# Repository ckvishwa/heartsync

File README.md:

# heartsync

Two matching, cloud-synced pixel-art devices for a couple. A heart sent from one
lights up the other. Working name; rename freely.

**Status:** Phases 1 (Display) and 2 (Cloud sync) of 11. See [docs/phases.md](docs/phases.md).

## Layout

| Folder      | What                                                        |
|-------------|-------------------------------------------------------------|
| `firmware/` | ESP32 firmware (PlatformIO, Arduino, C++17)                 |
| `cloud/`    | Firebase: rules, Cloud Functions (TypeScript), emulator     |
| `app/`      | Flutter app (iOS and Android)                               |
| `web/`      | Next.js dashboard: devices, pixel editor, OTA releases      |
| `cad/`      | Enclosure parameters, Fusion 360 scripts, print profiles    |
| `tools/`    | Repo-wide scripts (PNG to bitmap, couple seeding)           |
| `docs/`     | PRD, architecture, phases, protocol, ADRs, hardware notes   |

## Quick start

```sh
# Firmware (PlatformIO lives in the repo-local .venv)
python -m venv .venv && .venv/Scripts/pip install platformio cryptography pillow
cp firmware/include/secrets.example.h firmware/include/secrets.h   # then edit Wi-Fi
cd firmware && pio run && pio test -e native

# Cloud (emulators, offline, project id demo-heartsync)
cd cloud && npm install && npm --prefix functions install
npm run emulators          # terminal 1
npm run seed               # terminal 2: demo users, couple, devices
npm test                   # rules + sendHeart tests

# App (with the emulators running)
cd app && flutter run

# Web (with the emulators running)
cd web && npm install && npm run dev
```

Demo logins after seeding: `alice@example.com` and `bob@example.com`, password `heartsync`.

Start with [docs/prd.md](docs/prd.md), then [docs/architecture.md](docs/architecture.md).

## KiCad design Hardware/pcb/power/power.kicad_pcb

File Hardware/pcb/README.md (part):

# Ansonia rev A custom boards (rev G shell, 190 x 76 x 35.5)

Status (2026-11-23, after review 3): **schematics done (ERC 0 errors / 0 warnings on all four), placement done, routing INCOMPLETE:**
only the touch strip is routed; the carrier has its RF lines only; the power board and most of the carrier are not routed. See "Routing status".
DRC/ERC reports are in each board folder (`<board>_DRC.rpt`, `<board>_ERC.rpt`).

## Routing status (honest summary)

| Board | State |
|---|---|
| front_touch | **routed**, GND stitched; DRC: only `copper_sliver` from the hatched pour. Gerbers/BOM/CPL in `fab/` (still unverified by a fab DFM check). |
| front_sensor | routed with GND in the autorouter; **6 connections still open** (GND pads/zone islands, `front_sensor_DRC.rpt`). Gerbers withheld. |
| carrier | **only the three RF lines are routed** (hand-routed, DRC clean: no shorts/clearance; `tools/handroute.py`). The other 262 connections are **unrouted**. Freerouting 2.1.0 stalls at 110 unrouted (168 with the 0.5 mm power widths) and never ends, so no result could be imported. Gerbers withheld. |
| power | placement + In2 BAT_SW plane only: **unrouted** (210 connections). Freerouting not run on it (same stall expected). Gerbers withheld. |

What I would do next (not done): fan out the fine-pitch parts by hand (ESP32, SIM7080G, TCA9554s, TPS61088, IP5356M), pour +3V3/VSYS on In2 on the carrier,
hand-route PVDD / QB / IP_LX / BAT_* on the power board, then autoroute the remainder with a hard pass limit (the jar ignores `-mp`).
Tools: `tools/handroute.py`, `tools/route.py` (Freerouting 2.1.0 jar via DSN/SES, GND poured not routed, width cap per board), `tools/stitch.py`
(GND / pad stitching vias, pruned by DRC), `tools/export.py` (schematic PDF, Gerber+drill zip, JLCPCB BOM/CPL, renders).
Freerouting v2.5.0's CLI crashes (native-image serialization error) and v2.3+ needs Java 25, so the v2.1.0 jar from the project's GitHub release
(66,978,394 bytes, git-ignored `_vendor/freerouting/`) is used. RF width 0.2 mm is an estimate: recompute with the JLCPCB impedance calculator
for the real 1.0 mm 4-layer stack-up. Pi-match shunt pads (DNP) are connected by the autorouter later, not yet.

## DRC / ERC summary (reports in each board folder)

| Board | ERC err / warn | DRC items (refilled zones, schematic parity on) |
|---|---|---|
| carrier | 0 / 0 | silk_edge_clearance 6, silk_over_copper 151, silk_overlap 98, starved_thermal 3, unconnected_items 262 |
| power | 0 / 0 | isolated_copper 15, silk_edge_clearance 1, silk_over_copper 163, silk_overlap 103, starved_thermal 12, unconnected_items 220 |
| front_sensor | 0 / 0 | silk_over_copper 8, silk_overlap 6, starved_thermal 2, unconnected_items 6 |
| front_touch | 0 / 0 | copper_sliver 4 |

No courtyard, edge, drill, short or hole errors remain on any board; `unconnected_items` is the unrouted work above, the rest is silkscreen and starved thermals (cosmetic / to review).

## Layout of this folder

| Path | What |
|---|---|
| `carrier/`, `power/`, `front_sensor/`, `front_touch/` | One KiCad 10 project each (`.kicad_pro/.kicad_sch/.kicad_pcb`), ERC/DRC reports, `fab/` snapshots |
| `lib/ansonia.kicad_sym`, `lib/ansonia.pretty` | Project symbols and footprints (sources below) |
| `tools/` | Generators: the Python files ARE the source of the schematics and placement |
| `_vendor/` | Downloaded datasheets / vendor footprints (git-ignored, re-download from the links below) |

Regenerate (KiCad closed):

```
cd Hardware/pcb/tools
python build_sch.py                       # schematics + ERC + netlist cross-check (all boards)
"C:\Program Files\KiCad\10.0\bin\python.exe" lib_build_fp.py      # footprints (only if lib changed)
"C:\Program Files\KiCad\10.0\bin\python.exe" pcb_build.py carrier # board: outline, holes, placement
python snap.py carrier                    # placement PNGs + DRC (refills zones, schematic parity)
```

`designs.py` = circuits (values and their datasheet sources are in the sheet notes), `boards.py` =
outlines, holes, keep-outs, placement in **device mm** (origin = device centre, +X right end, +Y top
edge, seen from the front; KiCad origin (100, 100), Y flipped). Every board has F.Cu facing the front wall.
After routing starts, rebuild with `--keep-placement` (or stop regenerating the PCB and edit in KiCad).

## Boards

| Board | Outline (device mm) | Size | Stack | Notes |
|---|---|---|---|---|
| Carrier | X -62..+28, Y -17.5..+30 | 90 x 47.5 | 4L 1.0 mm (F sig / In1 GND / In2 PWR / B sig+GND) | grew left over the old SIM-board spot; all parts on the front side |
| Power | X 30..73 (Y > -1), X 30..66.5 (Y < -1), Y -16..+33 | 43 x 49 | 4L 1.6 mm, 2 oz outer | plain outline (lid notch removed: the lid is clipped, no screws); USB-C cut-outs in the top edge |
| Front sensor | X -72.0..-60.4, Y 24.0..34.3 | 11.6 x 10.3 | 2L 0.8 mm | 8 solder pads (1.2 mm pitch, back side) replace the JST: smaller than before (13.3 x 11.8) |
| Touch strip | X -56..-16, Y 27.25..32.25 | 40 x 5 | 2L 0.8 mm | no tab: 2 solder pads on the back at the right end |

### What moved vs the fit map / brief

- **Carrier mounting holes:** H1 (-41, 21) -> (-41, 20.5); H2 (-41, 4) unchanged; **H3 (1.5, 16) -> (-9, 16)**
  (the SIM7080G sits there now); **H4 (4.5, -12) -> (9, -12.5)** (clears the e-paper FPC). The bracket frame must follow.
- **Carrier connectors:** J1 right edge (24.6, 12.5) 20-pin; J4 spk L left edge (-58.7, -7); J6 haptic bottom
  (-50, -14.2); J7 touch (-46.5, 26.6); J8 front sensor (-56, 26.6); J9 mute LED (-58.7, -13.5); J11 panel FPC
  (-25.5, -13.4); J12 buttons (-38.35, 26.6); J13 e-paper FPC (-4, -13.4, DNP); J14 nano-SIM (20.5, -9.5).
  **Dropped:** J2 (cell sense: the PD IC gauges the cell over I2C), J3 (SIM board is now on the carrier),
  J5 (speaker R plugs into the power board, J7 there, next to the amp), J10 (gesture shares J8 with the mic:
  one front board, one cable).
- **Lid (review 1):** no screws any more (gasket + 8 snap clips at Z 0..4 + a hook into each speaker box). The boss
  notch and keep-outs are deleted; the power board is a full rectangle again.
- **Review-1 changes:** J1 is now 22-pin (adds QI_EN, PWR_KEY; footprint `ansonia:JST_SH_SM22B...` made from KiCad's
  SM20B, **verify against the JST drawing**); J5 dropped (NTC on J4); IMU U12 added; J13 e-paper fitted with booster.
- **USB-C ports:** centres X +52.75 / +66.05 as briefed, but the footprint puts the board edge 0.25 mm further
  out than Amphenol's drawing so the rear shell legs keep 0.3 mm copper-to-edge (Amphenol's layout has 0.05 mm).
  The port mating face therefore sits 0.25 mm further inside: check against the wall opening.

### Connector rule (review 2)

Wires are soldered straight to the small remote boards/parts (front sensor, touch strip, buttons, haptic LRA, mute LED): no connector on
that end. The carrier keeps one JST SH per remote (J8 front sensor 8-pin, J7 touch 2-pin, J12 buttons 6-pin, J6 haptic 2-pin, J9 mute LED
2-pin) so it can come out. Kept as connectors: U.FL x 4 antennas, FPC for the OLED (J11) and e-paper (J13), carrier-to-power J1, speakers
(carrier J4, power J7). Wire pads: `ansonia:WirePads_1x08_P1.20mm` (1.0 x 2.0 mm) and `_1x02_P1.60mm`.
Battery: **Amass MR30PW-M** on the power board J4 (left edge, mating face flush with X 30) plus a 2-pin SH (J5) for the NTC. The MR30 is a
3-pole part (the spec sheet I found: 15 A, 3.5 mm pitch, 3 x d1.9 holes + 2 x d1.0 locating holes); BAT+ on pin 1, BAT- on pin 3, pin 2
open. The 2-pin Amass part is the XT30: say if you meant that. Footprint holes are from the Amass drawing, body outline and the
locating-hole row position (10 mm from the pins) are my reading of it: **verify before fab**. The BAT solder pads were removed.

## Key circuit decisions (detail in the schematic sheet notes)

- **3 x TCA9554** (0x20 outputs, 0x21 buttons/status inputs, 0x22 Bluetooth control). The brief's expander list
  needs 20 I/O (6 outputs + 6 inputs + 4 BT PIOs + BT reset, SIM DTR, OLED VCC enable, mute LED); one TCA9554 has 8.
  Outputs that must be off at power-up have 10k pull-downs (TCA9554 inputs float high on 100k).
- **SIM7080G UART is 1.8 V** (VDD_EXT): TXB0104 between it and the ESP32 (TX, RX, STATUS, DTR). PWRKEY via MMBT3904.
- **Bluetooth antenna:** EWM104 pin 46 is a 50 ohm stamp hole and the module has **no antenna** (Ebyte manual 2.1).
  U.FL J17 + pi pads for a 2.4 GHz FPC antenna. Where that antenna goes is open.
- **ESP32 pin map:** checked against the WROOM-1U datasheet, no clash (IO35-37 unused, straps unused, IO19/20 USB).
  Spare: IO1, IO2 (test pads). USB D+/D- reach the ESP32 through J1 from USB-C port 1 for flashing.
- **12 V panel supply:** TPS61040 behind a P-FET switch so VCC floats when off (SSD1322 sec. 8.9).
- **Amp boost:** TPS61088 at **9.0 V** (499k / 76.8k), PWM mode, 600 kHz, values from the datasheet equations (sheet note). Amp limit 4 W/ch (see power budget).
- **Battery path:** MR30 J4 (BAT+ pin 1, BAT- pin 3; DNP 4x4 pads TP1/TP2 as an 18 AWG alternative) -> 8 A fuse -> reverse-battery P-FET
  (DMP3013SFV) -> BAT_SW (5 V TVS). Pack NTC on JST SH J5. **The IP5356M's VSYS pins are its internal 5-12 V DC-DC bus, not a system rail**:
  the system rail VSYS is the battery (BAT_SW) through a fitted 0R. Consequence: the system loads bypass the IC, so its fuel gauge does
  not see them and charge termination sees battery current net of the load. J1 now says VSYS = 3.0-4.2 V.
- **IMU (U12 LSM6DSOX, LGA-14):** I2C 0x6A (SA0 = GND, CS = VDDIO), INT1 -> ESP32 IO3 (RTC GPIO3, 100k pull-down so it is low at boot;
  IO3 is the JTAG-source strap, left at its default), INT2 -> TCA9554 0x21 P7. Placed at (-10, 8) mid-board, far from the speaker magnets.
  I2C map, no clash: 0x20/21/22 TCA9554, 0x2C TAS5805M, 0x39 APDS-9960, 0x5A DRV2605L, 0x6A LSM6DSOX; the power IC's address is TBD.
  Aux pins, from ST DS12814 rev 3 table 2 (p. 9), Mode 1 (aux SPI not used): pin 2 SDx and pin 3 SCx "Connect to VDDIO or GND" -> GND;
  pin 10 OCS_Aux "Leave unconnected" -> no connect; pin 11 SDO_Aux "Connect to VDD_IO or leave unconnected" -> VDDIO. (The pins have
  internal pull-ups, register bit "disable pull-up on OCS_Aux and SDO_Aux".) Symbol: modified KiCad LSM6DSL, identical LGA-14 pinout.
- **Qi TX:** separate 24 x 32 mm module on J6 (4-pin SH: 2 x QI_VIN 9 V, 2 x GND) with its **own TPS61088 boost (U7) and an LC filter**,
  see "Qi supply decision". Enable = QI_EN (expander 0x22 P6 over J1), which is U7's EN pin with a 10k pull-down.
- **E-paper (J13 fitted):** Waveshare 3.97inch e-Paper (G), 800 x 480, SSD2677, 24-pin 0.5 mm FPC. **Verified** against Waveshare's
  *3.97inch e-Paper (G) User Manual v1.0* (pin table sec. 5: identical to your list, pin 5 = VSH2) and the *3.97inch e-Paper HAT+ (G)* driver-board
  schematic (R1 2.2R, R2 1M, Q1 AO3400, L1 10uH, D1-D3 MBR0530, C1 4.7uF/25V on pin 5 VSH2, C2 1uF/50V on VDDIO+VCI, C4 1uF on VDD,
  C6-C9 4.7uF on VSH1/VGH/VSL/VGL, C10 1uF on VCOM, C3/C5 4.7uF). The two-colour panel has the same circuit. Pins 1/4/6/7 are NC, each its own
  net; pin 8 BS1 = GND (4-wire SPI). Differences to know: **BUSY is active low** (low = busy), **operating temperature 0..40 C**.
  FPC route (plan, not checked against the cell position in the fit map): the 24-pin tail leaves the panel's bottom edge, runs along the
  rear wall under the carrier's bottom edge (the carrier ends at Y -17.5, J13 enters from -Y) and folds once into J13; the cell and
  power board are on the +X side, so the tail should not cross the cell. Measure the tail length and fold radius on the real panel.
- **Bluetooth antenna:** 2.4 GHz FPC antenna on the inside of the BOTTOM wall, X +38..+64, Z 15..28 (above the pogo pads and the magnets
  at X +32/+70), far from the Wi-Fi PIFA (X -52..-12) and the LTE flex (top wall). J17 stays at the module (X -50): the U.FL
  cable is ~110 mm (about 1 dB at 2.4 GHz for 1.13 mm coax, estimate). It is near the Qi ferrite: test RSSI on the bench.
- **Front sensor acoustics:** the ICS-43434 library footprint already carries the 0.5 mm sound-port NPTH; it lands on (-69.5, 31.25),
  the front-wall hole. A ring-gasket outline (OD 3.6, ID 1.6) is drawn on F.Fab around it: foam/silicone ring between the PCB and the wall,
  airtight. APDS-9960 package centre at (-64, 31.25); its optical-window offset inside the package is not checked.

## IP5356M charger (review 3, item 1) - datasheet V1.00 read (IP5356M-datasheet-en-V1.00.pdf)

- **Cell count / power:** 1 cell (4.2/4.3/4.35/4.4 V), charge up to 18 W / 5 A at the battery, boost 5 V 3.1 A, 9 V 2.22 A, 12 V 1.67 A (p. 1).
- **Ports:** 2 USB-A, USB-B in, Micro/lightning in, **1 Type-C in/out** (PD2.0/3.0, PPS) and "1 USB C input/output port + 1 USB C output port
  (customize)" (p. 1). The datasheet's customised-model table (p. 10: LBZ, DBZ, DBZ_4V35, LCL, DCL1W, DCL1W_4V35) has **no dual-Type-C model
  and no part number for it**: ask Injoinic (service@injoinic.com) for the exact orderable name.
- **I2C:** only the `_L` (LED) models: **IP5356M_LBZ** (orderable at LCSC as **IP5356M_LBZ_CB, C46550232**) and IP5356M_LCL (with lightning).
  Pins: LED2 (pin 1) = SDA, LED1 (pin 40) = SCL, LED3 (pin 2) = INT; fig. 20 on p. 30: 3.3k from each of SDA/SCL to the IC's VCC and 510k from
  INT to ground; the IC enters I2C mode by itself from that wiring; INT is Hi-Z in standby and high when working. **The I2C slave address
  and the register map are NOT in this datasheet** (separate Injoinic document): not found. This design uses exactly fig. 20 and removes
  the carrier's 10k PWR_INT pull-up (it would hide the standby state).
- **NTC:** pin 22 sources 20 uA / 80 uA through the 10k NTC, 100 nF at the pin; if the NTC is absent a 10k to ground is required (p. 29-30, fig. 18).
  The pack's 10k NTC goes to J5. An unplugged J5 reads as "cold" and stops charging (safe).
- **Second Type-C (what I built):** port 2 = VOUT2 (pins 34/35, DPA2/DMA2 pins 32/33) to the J3 Type-C, 2.2 uF + 0.1 uF, Rp 22k from VBUS2 to
  CC1 and CC2 (1.5 A). Only 5 V when more than one port is on. **Open risk:** a real Type-C sink waits for VBUS before drawing current, but VOUT2
  turns on only when the IC detects a load: whether a plain Rd sink wakes it is not in the datasheet. The customised part may solve it: ask Injoinic.
- **Wiring used (datasheet fig. 25):** L1 2.2 uH LX to BAT, BST 0.1 uF to LX, VCC 2.2 uF, VSYS 6 x 22 uF (+0.1 uF), BAT 22 uF + 0.1 uF, VBUS 2 x 2.2 uF + 0.1 uF,
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
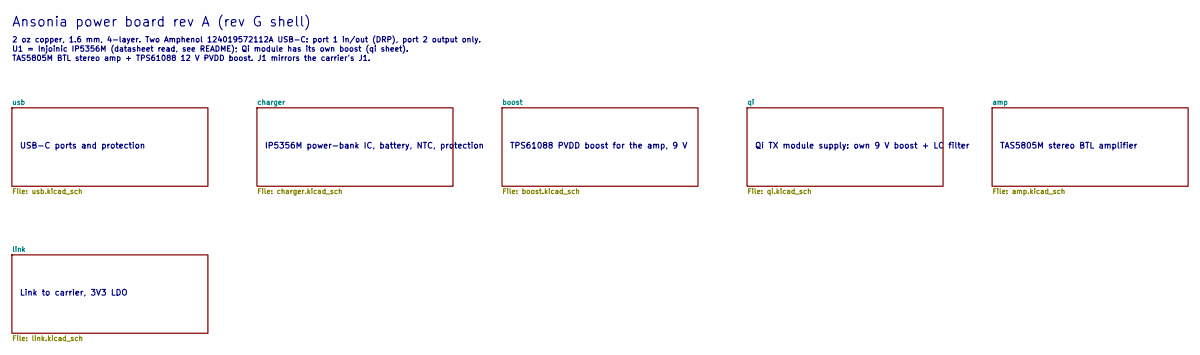
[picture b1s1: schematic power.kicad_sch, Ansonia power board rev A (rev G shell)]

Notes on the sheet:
USB-C ports and protection
IP5356M power-bank IC, battery, NTC, protection
TPS61088 PVDD boost for the amp, 9 V
Qi TX module supply: own 9 V boost + LC filter
TAS5805M stereo BTL amplifier
Link to carrier, 3V3 LDO
Ansonia power board rev A (rev G shell)
2 oz copper, 1.6 mm, 4-layer. Two Amphenol 124019572112A USB-C: port 1 in/out (DRP), port 2 output only.
U1 = Injoinic IP5356M (datasheet read, see README); Qi module has its own boost (qi sheet).
TAS5805M BTL stereo amp + TPS61088 12 V PVDD boost. J1 mirrors the carrier's J1.

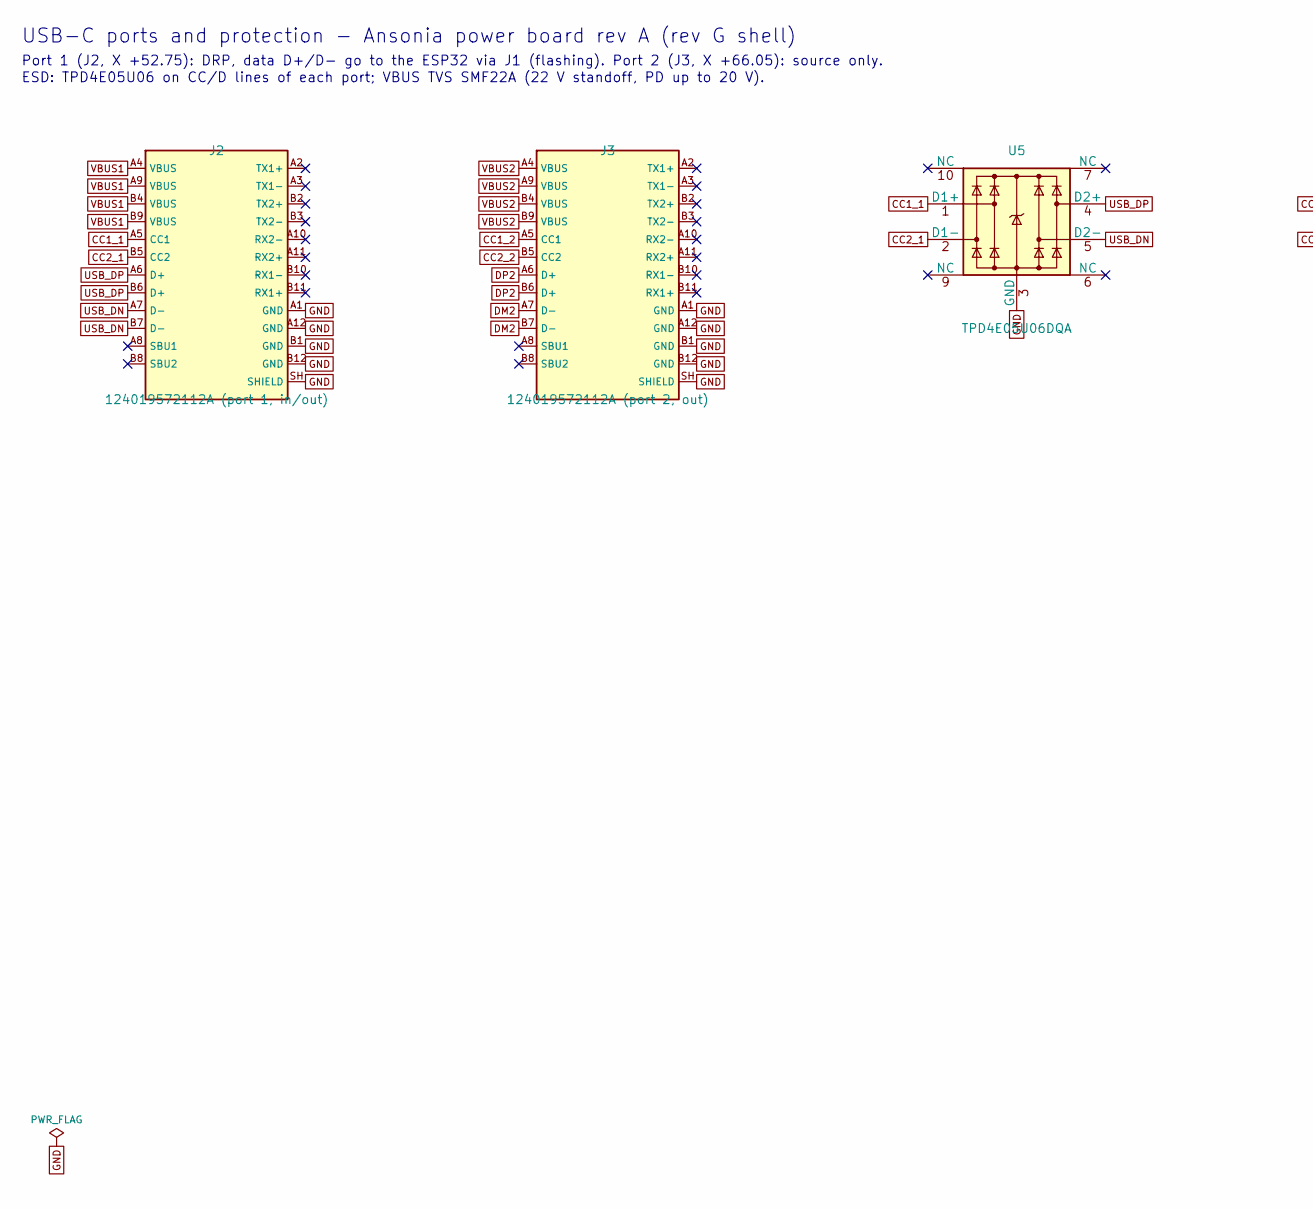
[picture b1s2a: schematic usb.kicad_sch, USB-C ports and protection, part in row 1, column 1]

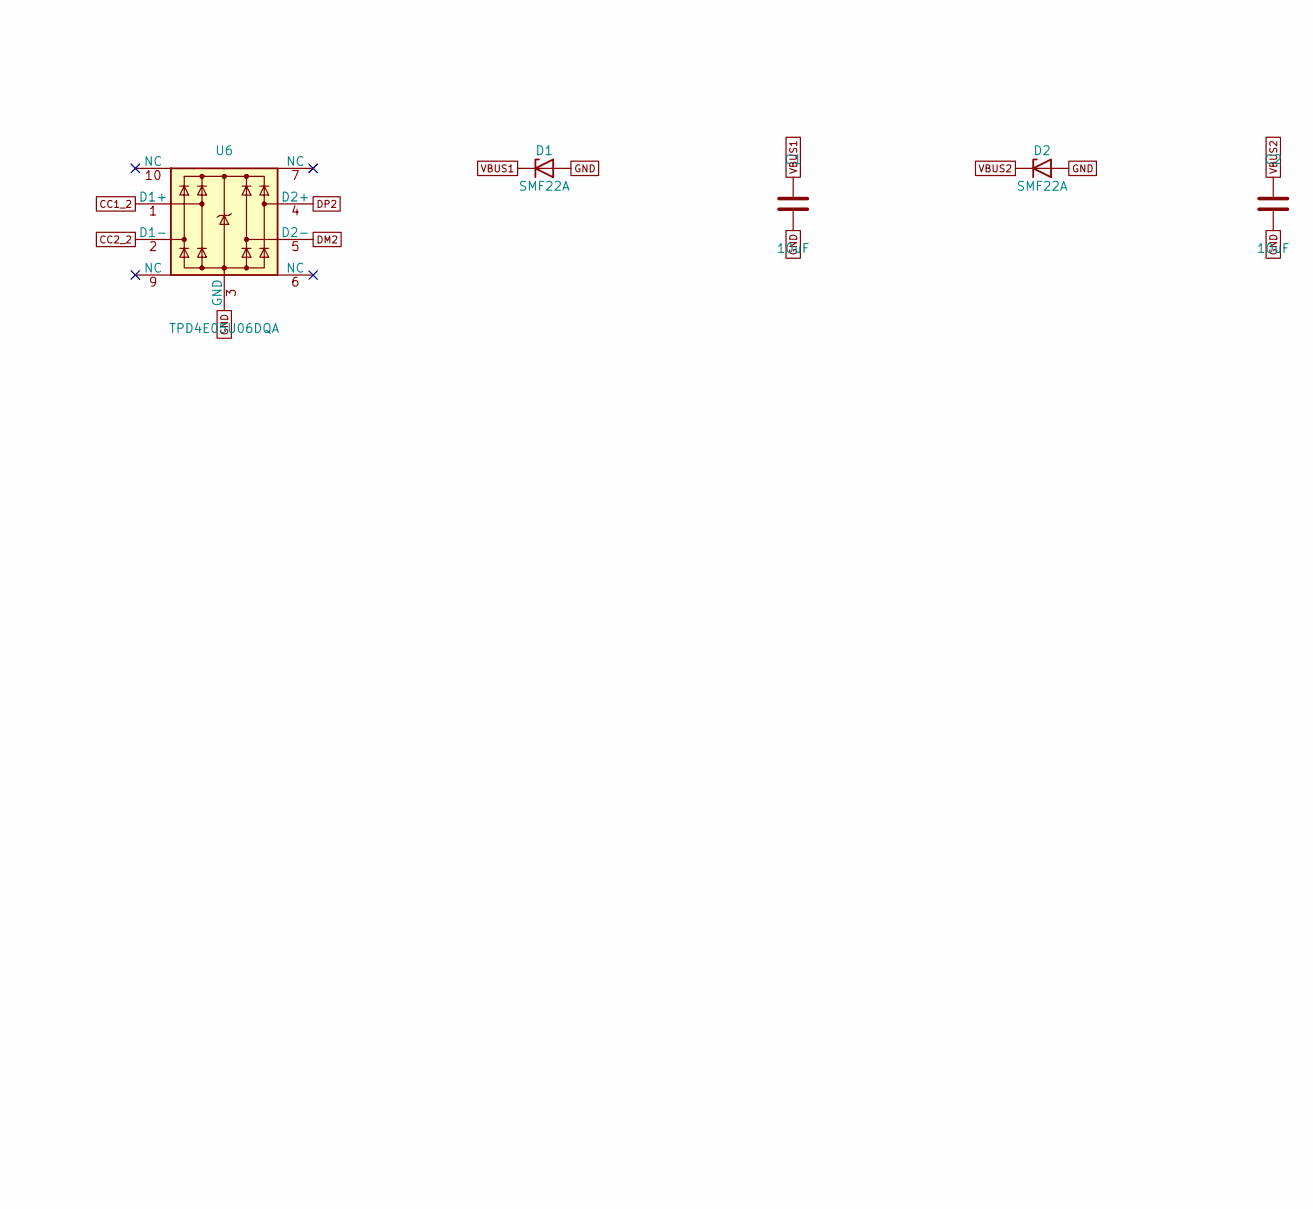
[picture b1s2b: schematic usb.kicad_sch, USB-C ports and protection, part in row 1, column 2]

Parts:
C1, C2: 10uF; C_0805_2012Metric
D1, D2: SMF22A; D_SOD-123F
J2: 124019572112A (port 1, in/out); USB_C_Amphenol_124019572112A; MPN 124019572112A
J3: 124019572112A (port 2, out); USB_C_Amphenol_124019572112A; MPN 124019572112A
U5, U6: TPD4E05U06DQA; USON-10_2.5x1.0mm_P0.5mm; MPN TPD4E05U06DQAR

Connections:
CC1_1: J2.A5 (CC1), U5.1 (D1+); also elsewhere on the board
CC1_2: J3.A5 (CC1), U6.1 (D1+); also elsewhere on the board
CC2_1: J2.B5 (CC2), U5.2 (D1-); also elsewhere on the board
CC2_2: J3.B5 (CC2), U6.2 (D1-); also elsewhere on the board
DM2: J3.A7 (D-), J3.B7 (D-), U6.5 (D2-); also elsewhere on the board
DP2: J3.A6 (D+), J3.B6 (D+), U6.4 (D2+); also elsewhere on the board
GND: C1.2, C2.2, D1.2 (A), D2.2 (A), J2.A1 (GND), J2.A12 (GND), J2.B1 (GND), J2.B12 (GND), J2.SH (SHIELD), J3.A1 (GND), J3.A12 (GND), J3.B1 (GND), J3.B12 (GND), J3.SH (SHIELD), U5.3 (GND), U5.8 (GND), U6.3 (GND), U6.8 (GND); also elsewhere on the board
USB_DN: J2.A7 (D-), J2.B7 (D-), U5.5 (D2-); also elsewhere on the board
USB_DP: J2.A6 (D+), J2.B6 (D+), U5.4 (D2+); also elsewhere on the board
VBUS1: C1.1, D1.1 (K), J2.A4 (VBUS), J2.A9 (VBUS), J2.B4 (VBUS), J2.B9 (VBUS); also elsewhere on the board
VBUS2: C2.1, D2.1 (K), J3.A4 (VBUS), J3.A9 (VBUS), J3.B4 (VBUS), J3.B9 (VBUS); also elsewhere on the board

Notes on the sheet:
USB-C ports and protection - Ansonia power board rev A (rev G shell)
Port 1 (J2, X +52.75): DRP, data D+/D- go to the ESP32 via J1 (flashing). Port 2 (J3, X +66.05): source only.
ESD: TPD4E05U06 on CC/D lines of each port; VBUS TVS SMF22A (22 V standoff, PD up to 20 V).

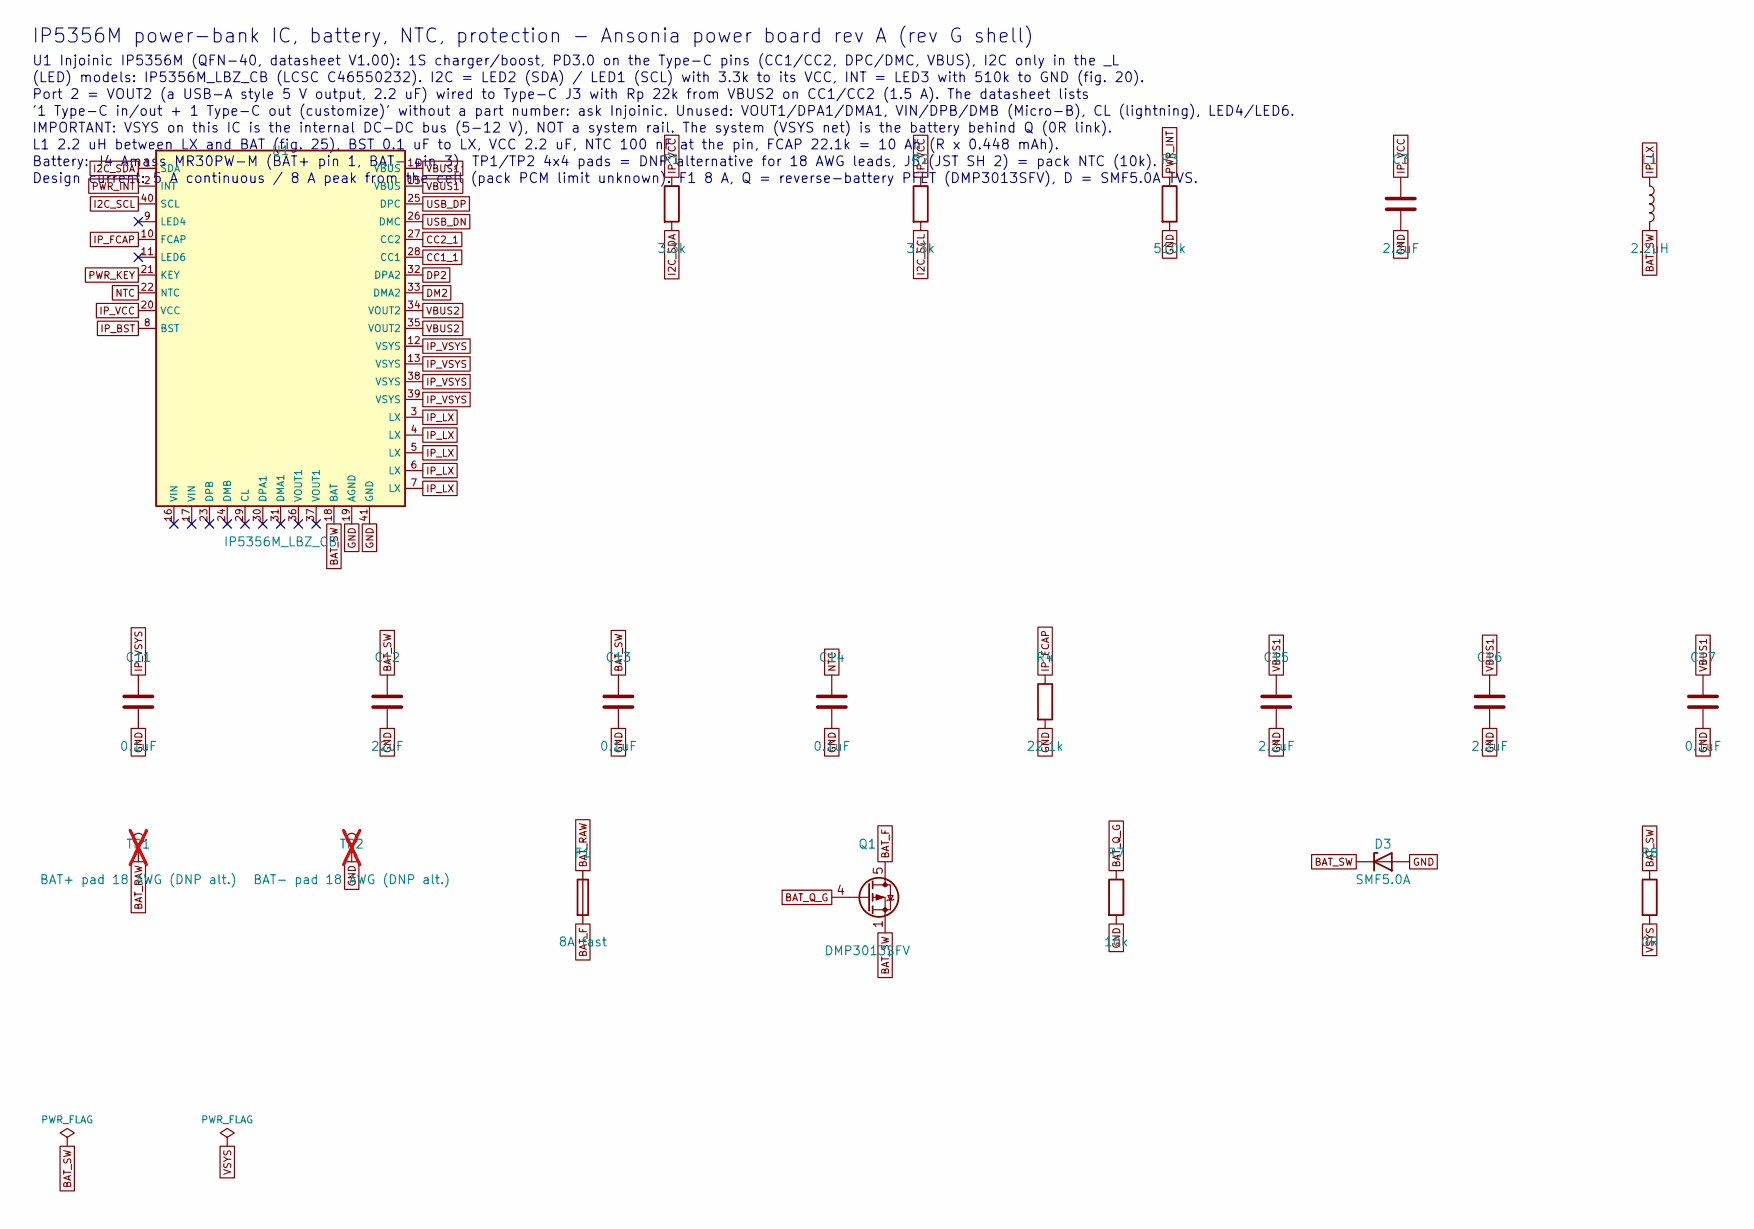
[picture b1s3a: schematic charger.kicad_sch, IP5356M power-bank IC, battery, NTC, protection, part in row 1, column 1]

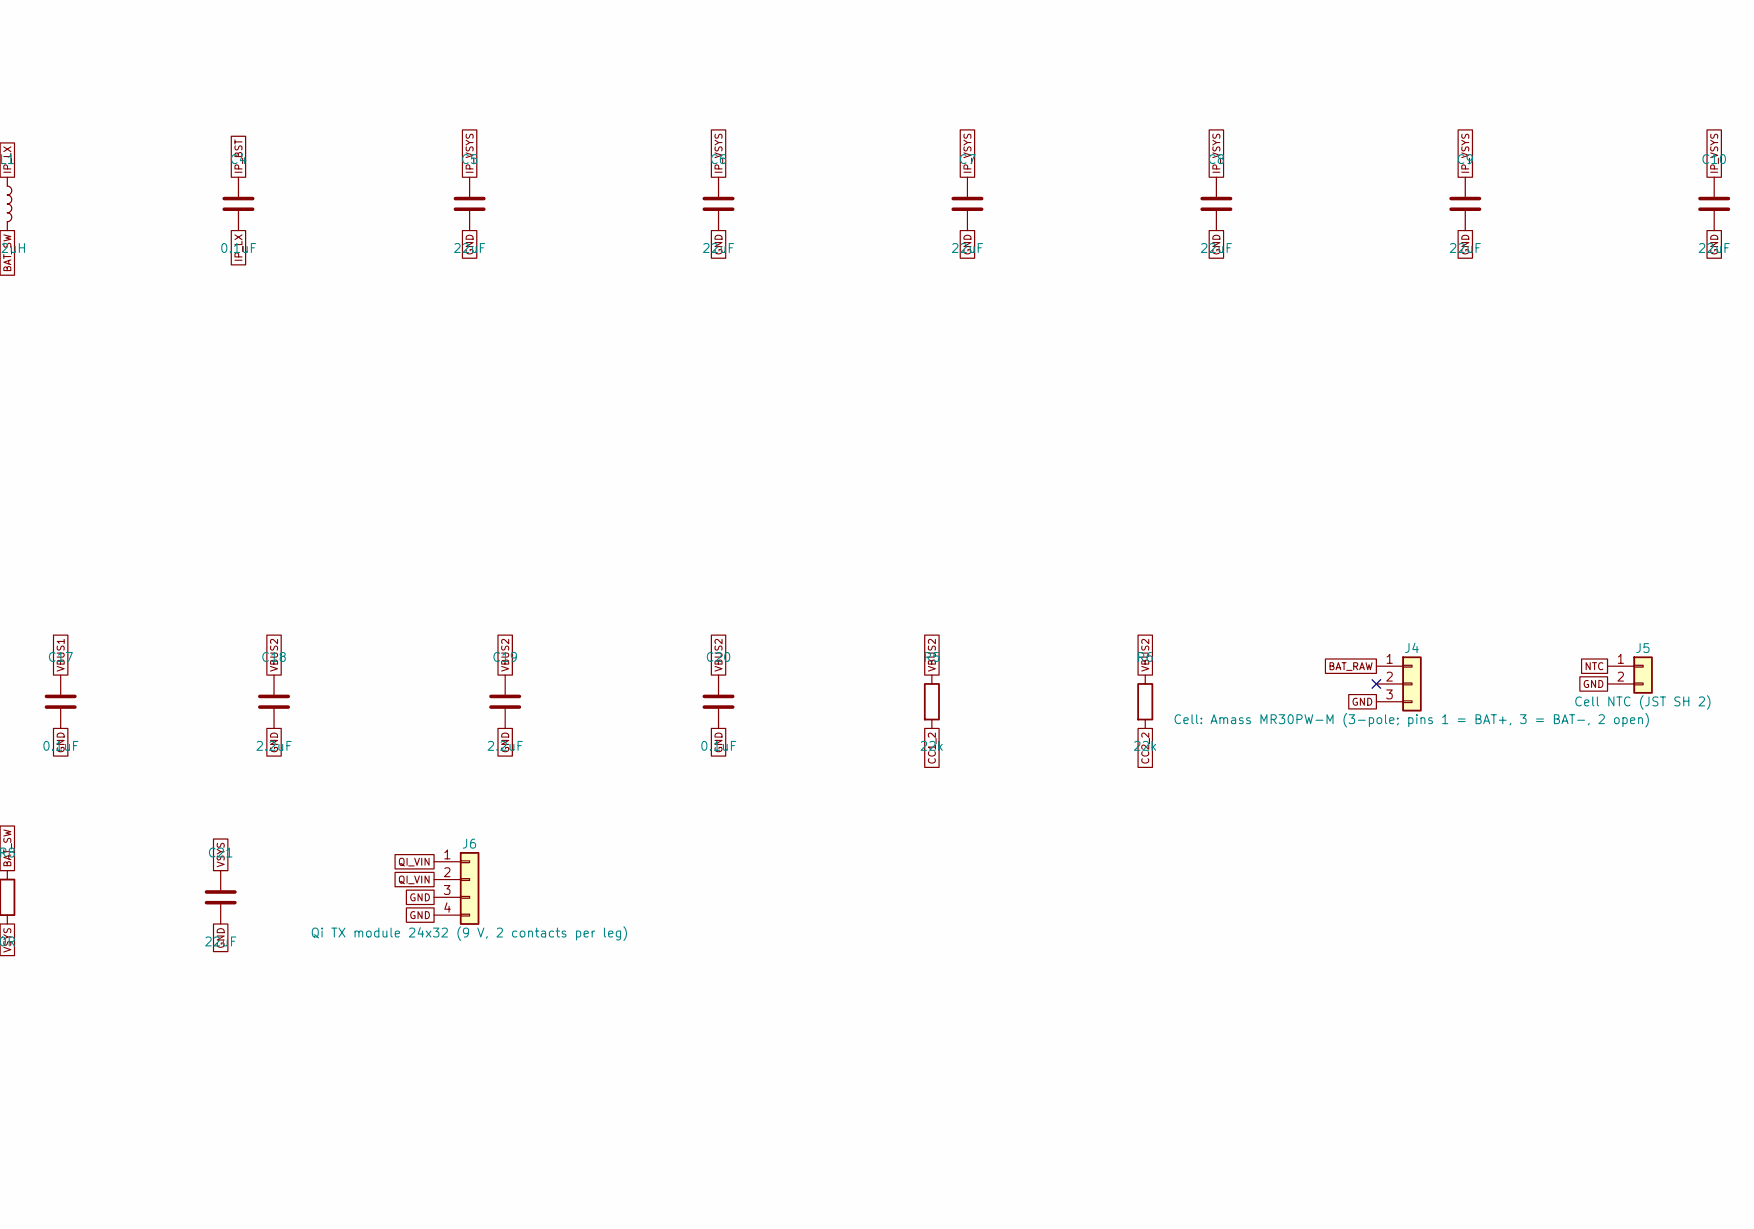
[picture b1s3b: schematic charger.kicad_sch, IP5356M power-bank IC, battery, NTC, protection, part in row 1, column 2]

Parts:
C3, C15, C16, C18, C19: 2.2uF; C_0603_1608Metric
C4, C11, C13, C14, C17, C20: 0.1uF; C_0402_1005Metric
C5, C6, C7, C8, C9, C10, C12, C21: 22uF; C_0805_2012Metric
D3: SMF5.0A; D_SOD-123F
F1: 8A fast; Fuse_1206_3216Metric; MPN 0466008.NR
J4: Cell: Amass MR30PW-M (3-pole; pins 1 = BAT+, 3 = 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; Amass_MR30PW-M_1x03_P3.50mm_Horizontal; MPN MR30PW-M
J5: Cell NTC (JST SH 2); JST_SH_SM02B-SRSS-TB_1x02-1MP_P1.00mm_Horizontal
J6: Qi TX module 24x32 (9 V, 2 contacts per leg); JST_SH_SM04B-SRSS-TB_1x04-1MP_P1.00mm_Horizontal
L1: 2.2uH; L_Bourns_SRP7028A_7.3x6.6mm; MPN SRP7028A-2R2M
Q1: DMP3013SFV; Diodes_PowerDI3333-8
R1, R2: 3.3k; R_0402_1005Metric
R3: 510k; R_0402_1005Metric
R4: 22.1k; R_0402_1005Metric
R5, R6: 22k; R_0402_1005Metric
R7: 10k; R_0402_1005Metric
R8: 0R; R_1206_3216Metric
TP1: BAT+ pad 18 AWG (DNP alt.); TestPoint_Pad_4.0x4.0mm; not fitted
TP2: BAT- pad 18 AWG (DNP alt.); TestPoint_Pad_4.0x4.0mm; not fitted
U1: IP5356M_LBZ_CB; QFN-40-1EP_6x6mm_P0.5mm_EP4.6x4.6mm; MPN IP5356M_LBZ_CB; LCSC C46550232

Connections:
BAT_F: F1.2, Q1.5 (D)
BAT_Q_G: Q1.4 (G), R7.1
BAT_RAW: F1.1, J4.1, TP1.1
BAT_SW: C12.1, C13.1, D3.1 (K), L1.2, Q1.1 (S), Q1.2 (S), Q1.3 (S), R8.1, U1.18 (BAT); also elsewhere on the board
CC1_1: U1.28 (CC1); also elsewhere on the board
CC1_2: R5.2; also elsewhere on the board
CC2_1: U1.27 (CC2); also elsewhere on the board
CC2_2: R6.2; also elsewhere on the board
DM2: U1.33 (DMA2); also elsewhere on the board
DP2: U1.32 (DPA2); also elsewhere on the board
GND: C3.2, C5.2, C6.2, C7.2, C8.2, C9.2, C10.2, C11.2, C12.2, C13.2, C14.2, C15.2, C16.2, C17.2, C18.2, C19.2, C20.2, C21.2, D3.2 (A), J4.3, J5.2, J6.3, J6.4, R3.2, R4.2, R7.2, TP2.1, U1.19 (AGND), U1.41 (GND); also elsewhere on the board
I2C_SCL: R2.2, U1.40 (SCL); also elsewhere on the board
I2C_SDA: R1.2, U1.1 (SDA); also elsewhere on the board
IP_BST: C4.1, U1.8 (BST)
IP_FCAP: R4.1, U1.10 (FCAP)
IP_LX: C4.2, L1.1, U1.3 (LX), U1.4 (LX), U1.5 (LX), U1.6 (LX), U1.7 (LX)
IP_VCC: C3.1, R1.1, R2.1, U1.20 (VCC)
IP_VSYS: C5.1, C6.1, C7.1, C8.1, C9.1, C10.1, C11.1, U1.12 (VSYS), U1.13 (VSYS), U1.38 (VSYS), U1.39 (VSYS)
NTC: C14.1, J5.1, U1.22 (NTC)
PWR_INT: R3.1, U1.2 (INT); also elsewhere on the board
PWR_KEY: U1.21 (KEY); also elsewhere on the board
QI_VIN: J6.1, J6.2; also elsewhere on the board
USB_DN: U1.26 (DMC); also elsewhere on the board
USB_DP: U1.25 (DPC); also elsewhere on the board
VBUS1: C15.1, C16.1, C17.1, U1.14 (VBUS), U1.15 (VBUS); also elsewhere on the board
VBUS2: C18.1, C19.1, C20.1, R5.1, R6.1, U1.34 (VOUT2), U1.35 (VOUT2); also elsewhere on the board
VSYS: C21.1, R8.2; also elsewhere on the board

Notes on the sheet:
IP5356M power-bank IC, battery, NTC, protection - Ansonia power board rev A (rev G shell)
U1 Injoinic IP5356M (QFN-40, datasheet V1.00): 1S charger/boost, PD3.0 on the Type-C pins (CC1/CC2, DPC/DMC, VBUS), I2C only in the _L
(LED) models: IP5356M_LBZ_CB (LCSC C46550232). I2C = LED2 (SDA) / LED1 (SCL) with 3.3k to its VCC, INT = LED3 with 510k to GND (fig. 20).
Port 2 = VOUT2 (a USB-A style 5 V output, 2.2 uF) wired to Type-C J3 with Rp 22k from VBUS2 on CC1/CC2 (1.5 A). The datasheet lists
'1 Type-C in/out + 1 Type-C out (customize)' without a part number: ask Injoinic. Unused: VOUT1/DPA1/DMA1, VIN/DPB/DMB (Micro-B), CL (lightning), LED4/LED6.
IMPORTANT: VSYS on this IC is the internal DC-DC bus (5-12 V), NOT a system rail. The system (VSYS net) is the battery behind Q (0R link).
L1 2.2 uH between LX and BAT (fig. 25), BST 0.1 uF to LX, VCC 2.2 uF, NTC 100 nF at the pin, FCAP 22.1k = 10 Ah (R x 0.448 mAh).
Battery: J4 Amass MR30PW-M (BAT+ pin 1, BAT- pin 3), TP1/TP2 4x4 pads = DNP alternative for 18 AWG leads, J5 (JST SH 2) = pack NTC (10k).
Design current: 5 A continuous / 8 A peak from the cell (pack PCM limit unknown). F1 8 A, Q = reverse-battery PFET (DMP3013SFV), D = SMF5.0A TVS.

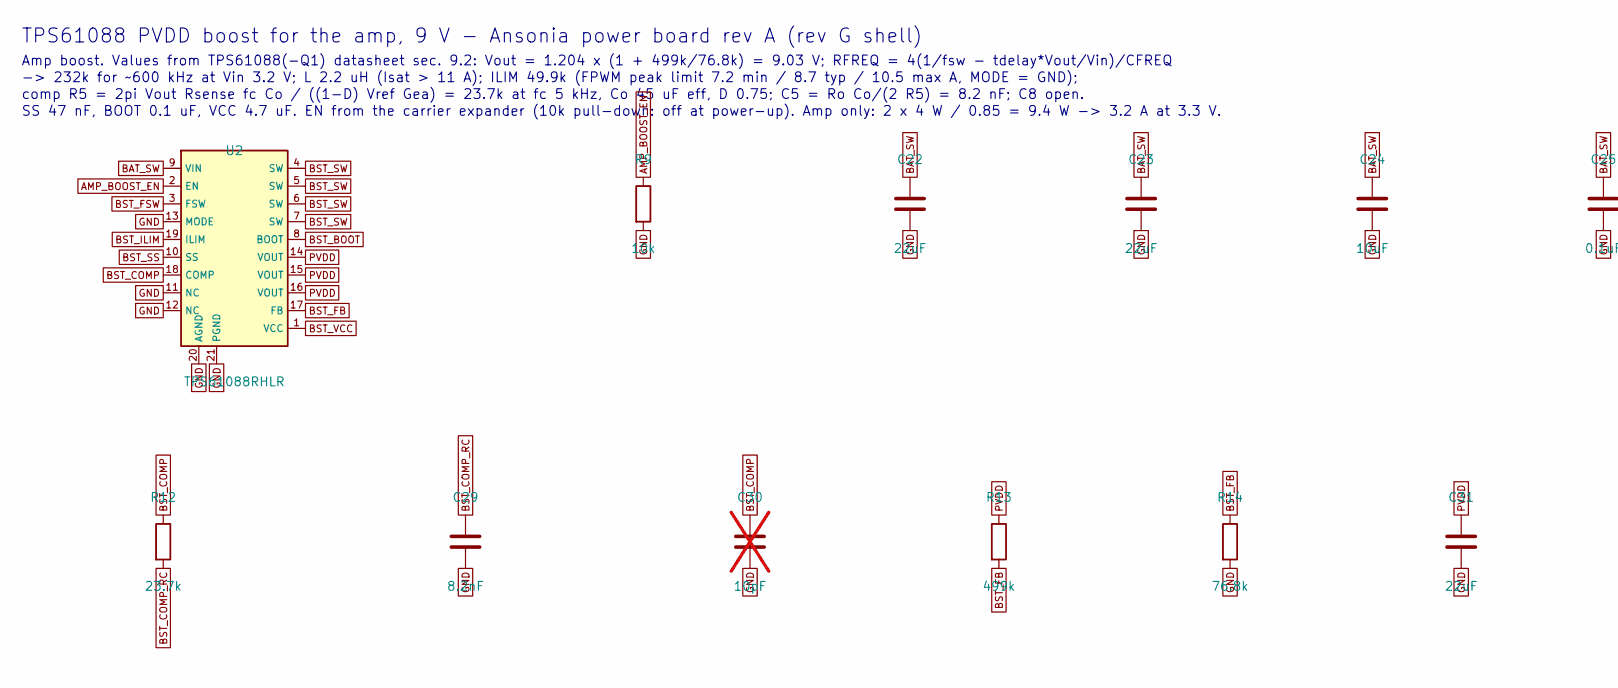
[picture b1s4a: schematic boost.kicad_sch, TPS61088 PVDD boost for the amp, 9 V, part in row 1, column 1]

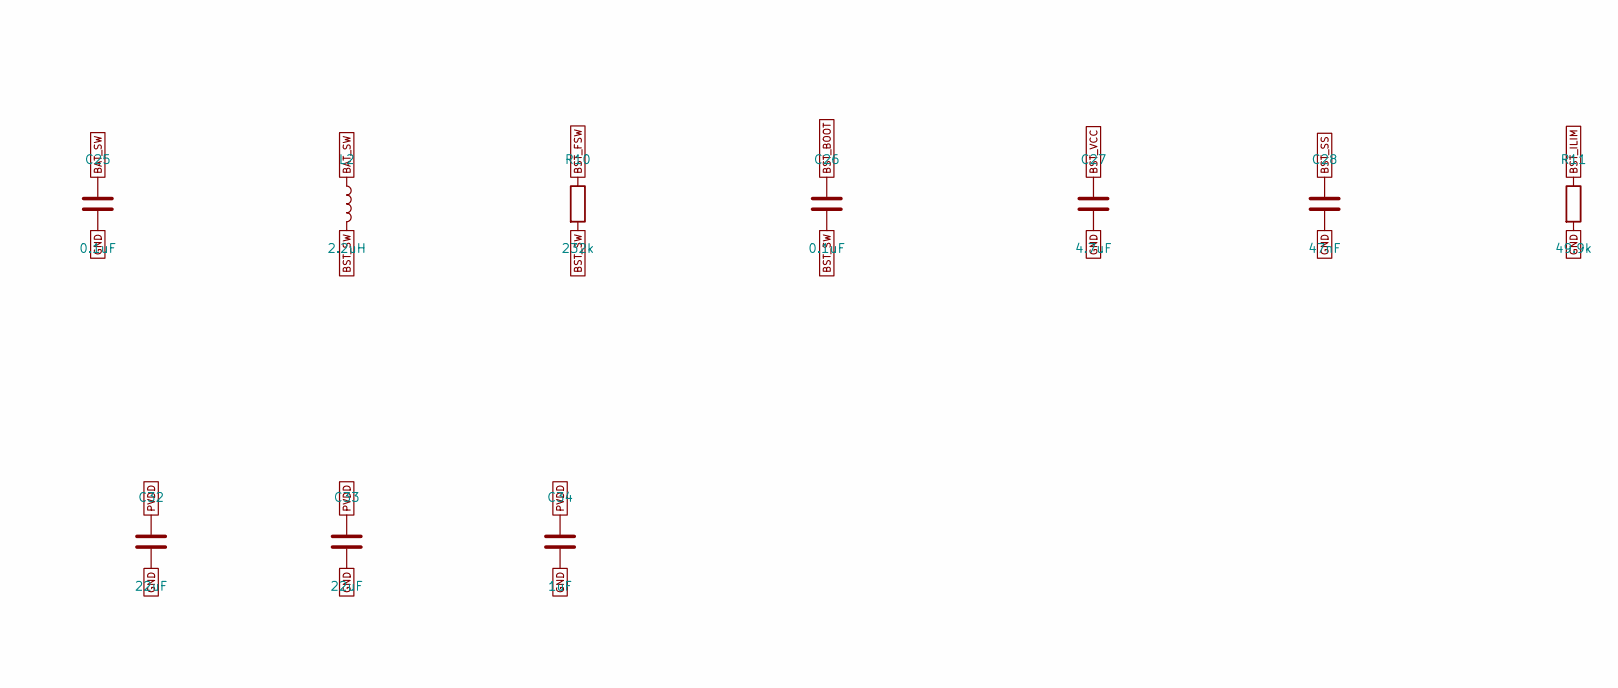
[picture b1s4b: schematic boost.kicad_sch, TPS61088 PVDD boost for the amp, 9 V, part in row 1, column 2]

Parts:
C22, C23: 22uF; C_0805_2012Metric
C24: 10uF; C_0603_1608Metric
C25, C26: 0.1uF; C_0402_1005Metric
C27: 4.7uF; C_0603_1608Metric
C28: 47nF; C_0402_1005Metric
C29: 8.2nF; C_0402_1005Metric
C30: 10pF; C_0402_1005Metric; not fitted
C31, C32, C33: 22uF; C_1206_3216Metric
C34: 1uF; C_0603_1608Metric
L2: 2.2uH; L_Bourns_SRP7028A_7.3x6.6mm; MPN SRP7028A-2R2M
R9: 10k; R_0402_1005Metric
R10: 232k; R_0402_1005Metric
R11: 49.9k; R_0402_1005Metric
R12: 23.7k; R_0402_1005Metric
R13: 499k; R_0402_1005Metric
R14: 76.8k; R_0402_1005Metric
U2: TPS61088RHLR; Texas_VQFN-RHL-20; MPN TPS61088RHLR; LCSC C88281

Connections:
AMP_BOOST_EN: R9.1, U2.2 (EN); also elsewhere on the board
BAT_SW: C22.1, C23.1, C24.1, C25.1, L2.1, U2.9 (VIN); also elsewhere on the board
BST_BOOT: C26.1, U2.8 (BOOT)
BST_COMP: C30.1, R12.1, U2.18 (COMP)
BST_COMP_RC: C29.1, R12.2
BST_FB: R13.2, R14.1, U2.17 (FB)
BST_FSW: R10.1, U2.3 (FSW)
BST_ILIM: R11.1, U2.19 (ILIM)
BST_SS: C28.1, U2.10 (SS)
BST_SW: C26.2, L2.2, R10.2, U2.4 (SW), U2.5 (SW), U2.6 (SW), U2.7 (SW)
BST_VCC: C27.1, U2.1 (VCC)
GND: C22.2, C23.2, C24.2, C25.2, C27.2, C28.2, C29.2, C30.2, C31.2, C32.2, C33.2, C34.2, R9.2, R11.2, R14.2, U2.11 (NC), U2.12 (NC), U2.13 (MODE), U2.20 (AGND), U2.21 (PGND); also elsewhere on the board
PVDD: C31.1, C32.1, C33.1, C34.1, R13.1, U2.14 (VOUT), U2.15 (VOUT), U2.16 (VOUT); also elsewhere on the board

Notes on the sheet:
TPS61088 PVDD boost for the amp, 9 V - Ansonia power board rev A (rev G shell)
Amp boost. Values from TPS61088(-Q1) datasheet sec. 9.2: Vout = 1.204 x (1 + 499k/76.8k) = 9.03 V; RFREQ = 4(1/fsw - tdelay*Vout/Vin)/CFREQ
-> 232k for ~600 kHz at Vin 3.2 V; L 2.2 uH (Isat > 11 A); ILIM 49.9k (FPWM peak limit 7.2 min / 8.7 typ / 10.5 max A, MODE = GND);
comp R5 = 2pi Vout Rsense fc Co / ((1-D) Vref Gea) = 23.7k at fc 5 kHz, Co 45 uF eff, D 0.75; C5 = Ro Co/(2 R5) = 8.2 nF; C8 open.
SS 47 nF, BOOT 0.1 uF, VCC 4.7 uF. EN from the carrier expander (10k pull-down: off at power-up). Amp only: 2 x 4 W / 0.85 = 9.4 W -> 3.2 A at 3.3 V.

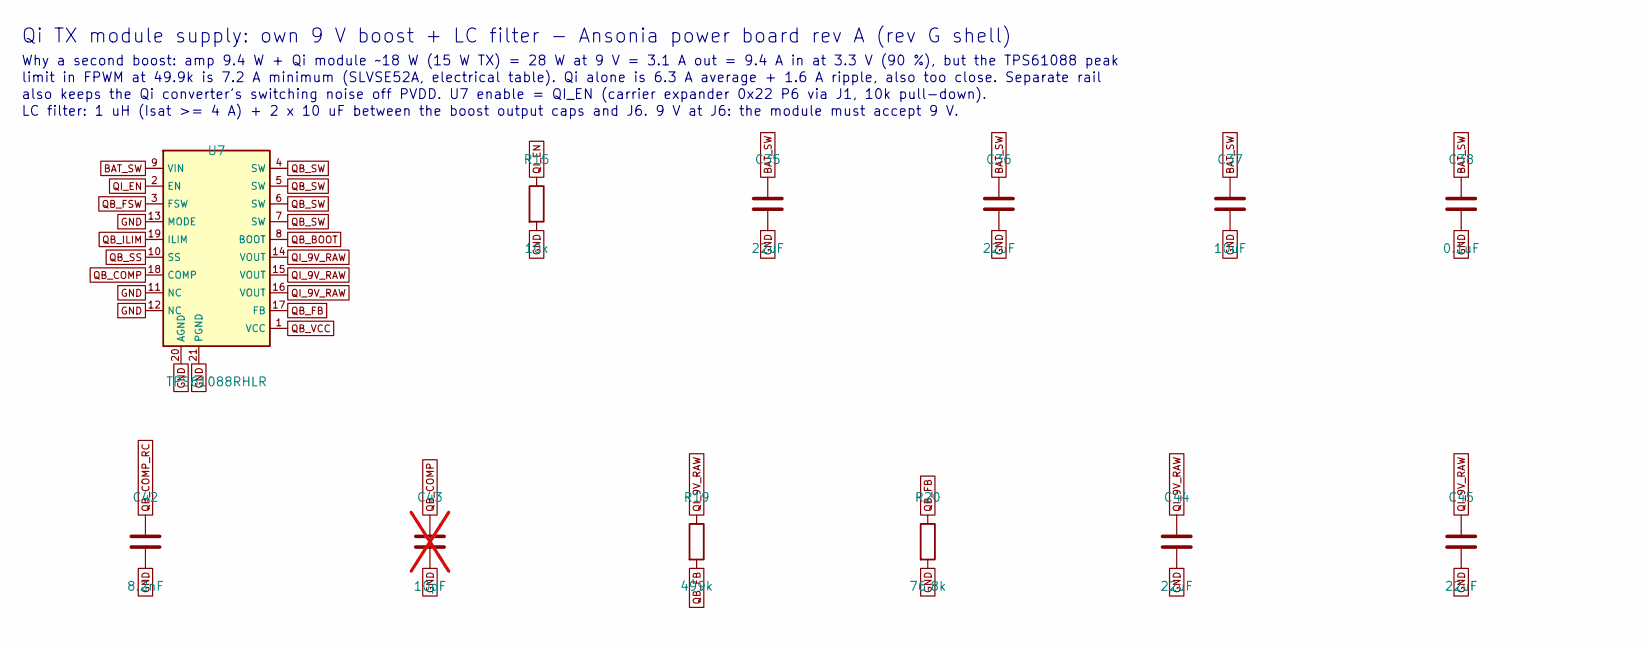
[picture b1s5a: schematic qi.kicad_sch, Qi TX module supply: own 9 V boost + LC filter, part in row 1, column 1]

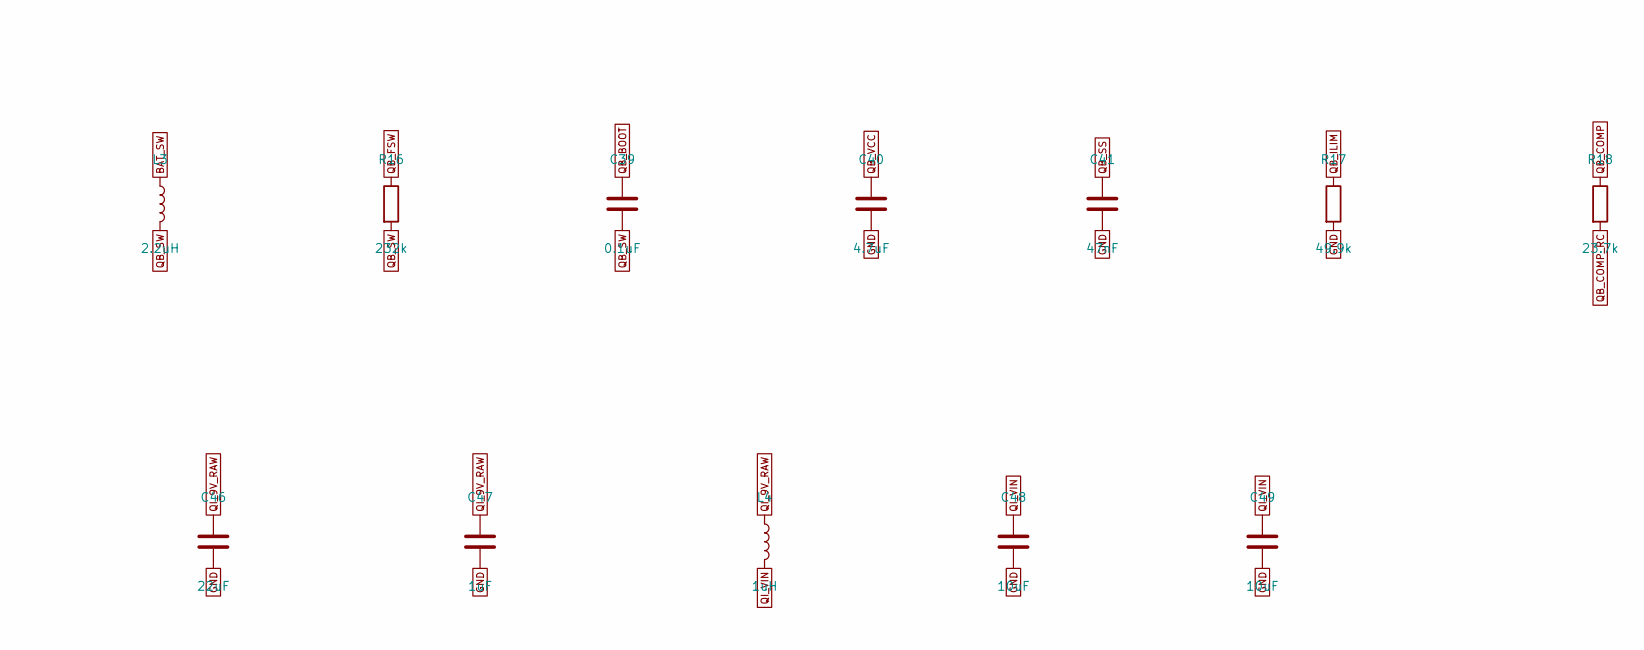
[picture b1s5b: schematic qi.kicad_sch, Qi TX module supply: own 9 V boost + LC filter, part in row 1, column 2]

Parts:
C35, C36: 22uF; C_0805_2012Metric
C37: 10uF; C_0603_1608Metric
C38, C39: 0.1uF; C_0402_1005Metric
C40: 4.7uF; C_0603_1608Metric
C41: 47nF; C_0402_1005Metric
C42: 8.2nF; C_0402_1005Metric
C43: 10pF; C_0402_1005Metric; not fitted
C44, C45, C46: 22uF; C_1206_3216Metric
C47: 1uF; C_0603_1608Metric
C48, C49: 10uF; C_0805_2012Metric
L3: 2.2uH; L_Bourns_SRP7028A_7.3x6.6mm; MPN SRP7028A-2R2M
L4: 1uH; L_1210_3225Metric; MPN DFE322520F-1R0M
R15: 10k; R_0402_1005Metric
R16: 232k; R_0402_1005Metric
R17: 49.9k; R_0402_1005Metric
R18: 23.7k; R_0402_1005Metric
R19: 499k; R_0402_1005Metric
R20: 76.8k; R_0402_1005Metric
U7: TPS61088RHLR; Texas_VQFN-RHL-20; MPN TPS61088RHLR; LCSC C88281

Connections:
BAT_SW: C35.1, C36.1, C37.1, C38.1, L3.1, U7.9 (VIN); also elsewhere on the board
GND: C35.2, C36.2, C37.2, C38.2, C40.2, C41.2, C42.2, C43.2, C44.2, C45.2, C46.2, C47.2, C48.2, C49.2, R15.2, R17.2, R20.2, U7.11 (NC), U7.12 (NC), U7.13 (MODE), U7.20 (AGND), U7.21 (PGND); also elsewhere on the board
QB_BOOT: C39.1, U7.8 (BOOT)
QB_COMP: C43.1, R18.1, U7.18 (COMP)
QB_COMP_RC: C42.1, R18.2
QB_FB: R19.2, R20.1, U7.17 (FB)
QB_FSW: R16.1, U7.3 (FSW)
QB_ILIM: R17.1, U7.19 (ILIM)
QB_SS: C41.1, U7.10 (SS)
QB_SW: C39.2, L3.2, R16.2, U7.4 (SW), U7.5 (SW), U7.6 (SW), U7.7 (SW)
QB_VCC: C40.1, U7.1 (VCC)
QI_9V_RAW: C44.1, C45.1, C46.1, C47.1, L4.1, R19.1, U7.14 (VOUT), U7.15 (VOUT), U7.16 (VOUT)
QI_EN: R15.1, U7.2 (EN); also elsewhere on the board
QI_VIN: C48.1, C49.1, L4.2; also elsewhere on the board

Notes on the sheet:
Qi TX module supply: own 9 V boost + LC filter - Ansonia power board rev A (rev G shell)
Why a second boost: amp 9.4 W + Qi module ~18 W (15 W TX) = 28 W at 9 V = 3.1 A out = 9.4 A in at 3.3 V (90 %), but the TPS61088 peak
limit in FPWM at 49.9k is 7.2 A minimum (SLVSE52A, electrical table). Qi alone is 6.3 A average + 1.6 A ripple, also too close. Separate rail
also keeps the Qi converter's switching noise off PVDD. U7 enable = QI_EN (carrier expander 0x22 P6 via J1, 10k pull-down).
LC filter: 1 uH (Isat >= 4 A) + 2 x 10 uF between the boost output caps and J6. 9 V at J6: the module must accept 9 V.

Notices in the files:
Hardware/pcb/tools/designs.py:
"""Ansonia rev G board circuits. Values cite their source in the sheet notes.
